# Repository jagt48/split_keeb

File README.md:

# split_keeb
Split keyboard design

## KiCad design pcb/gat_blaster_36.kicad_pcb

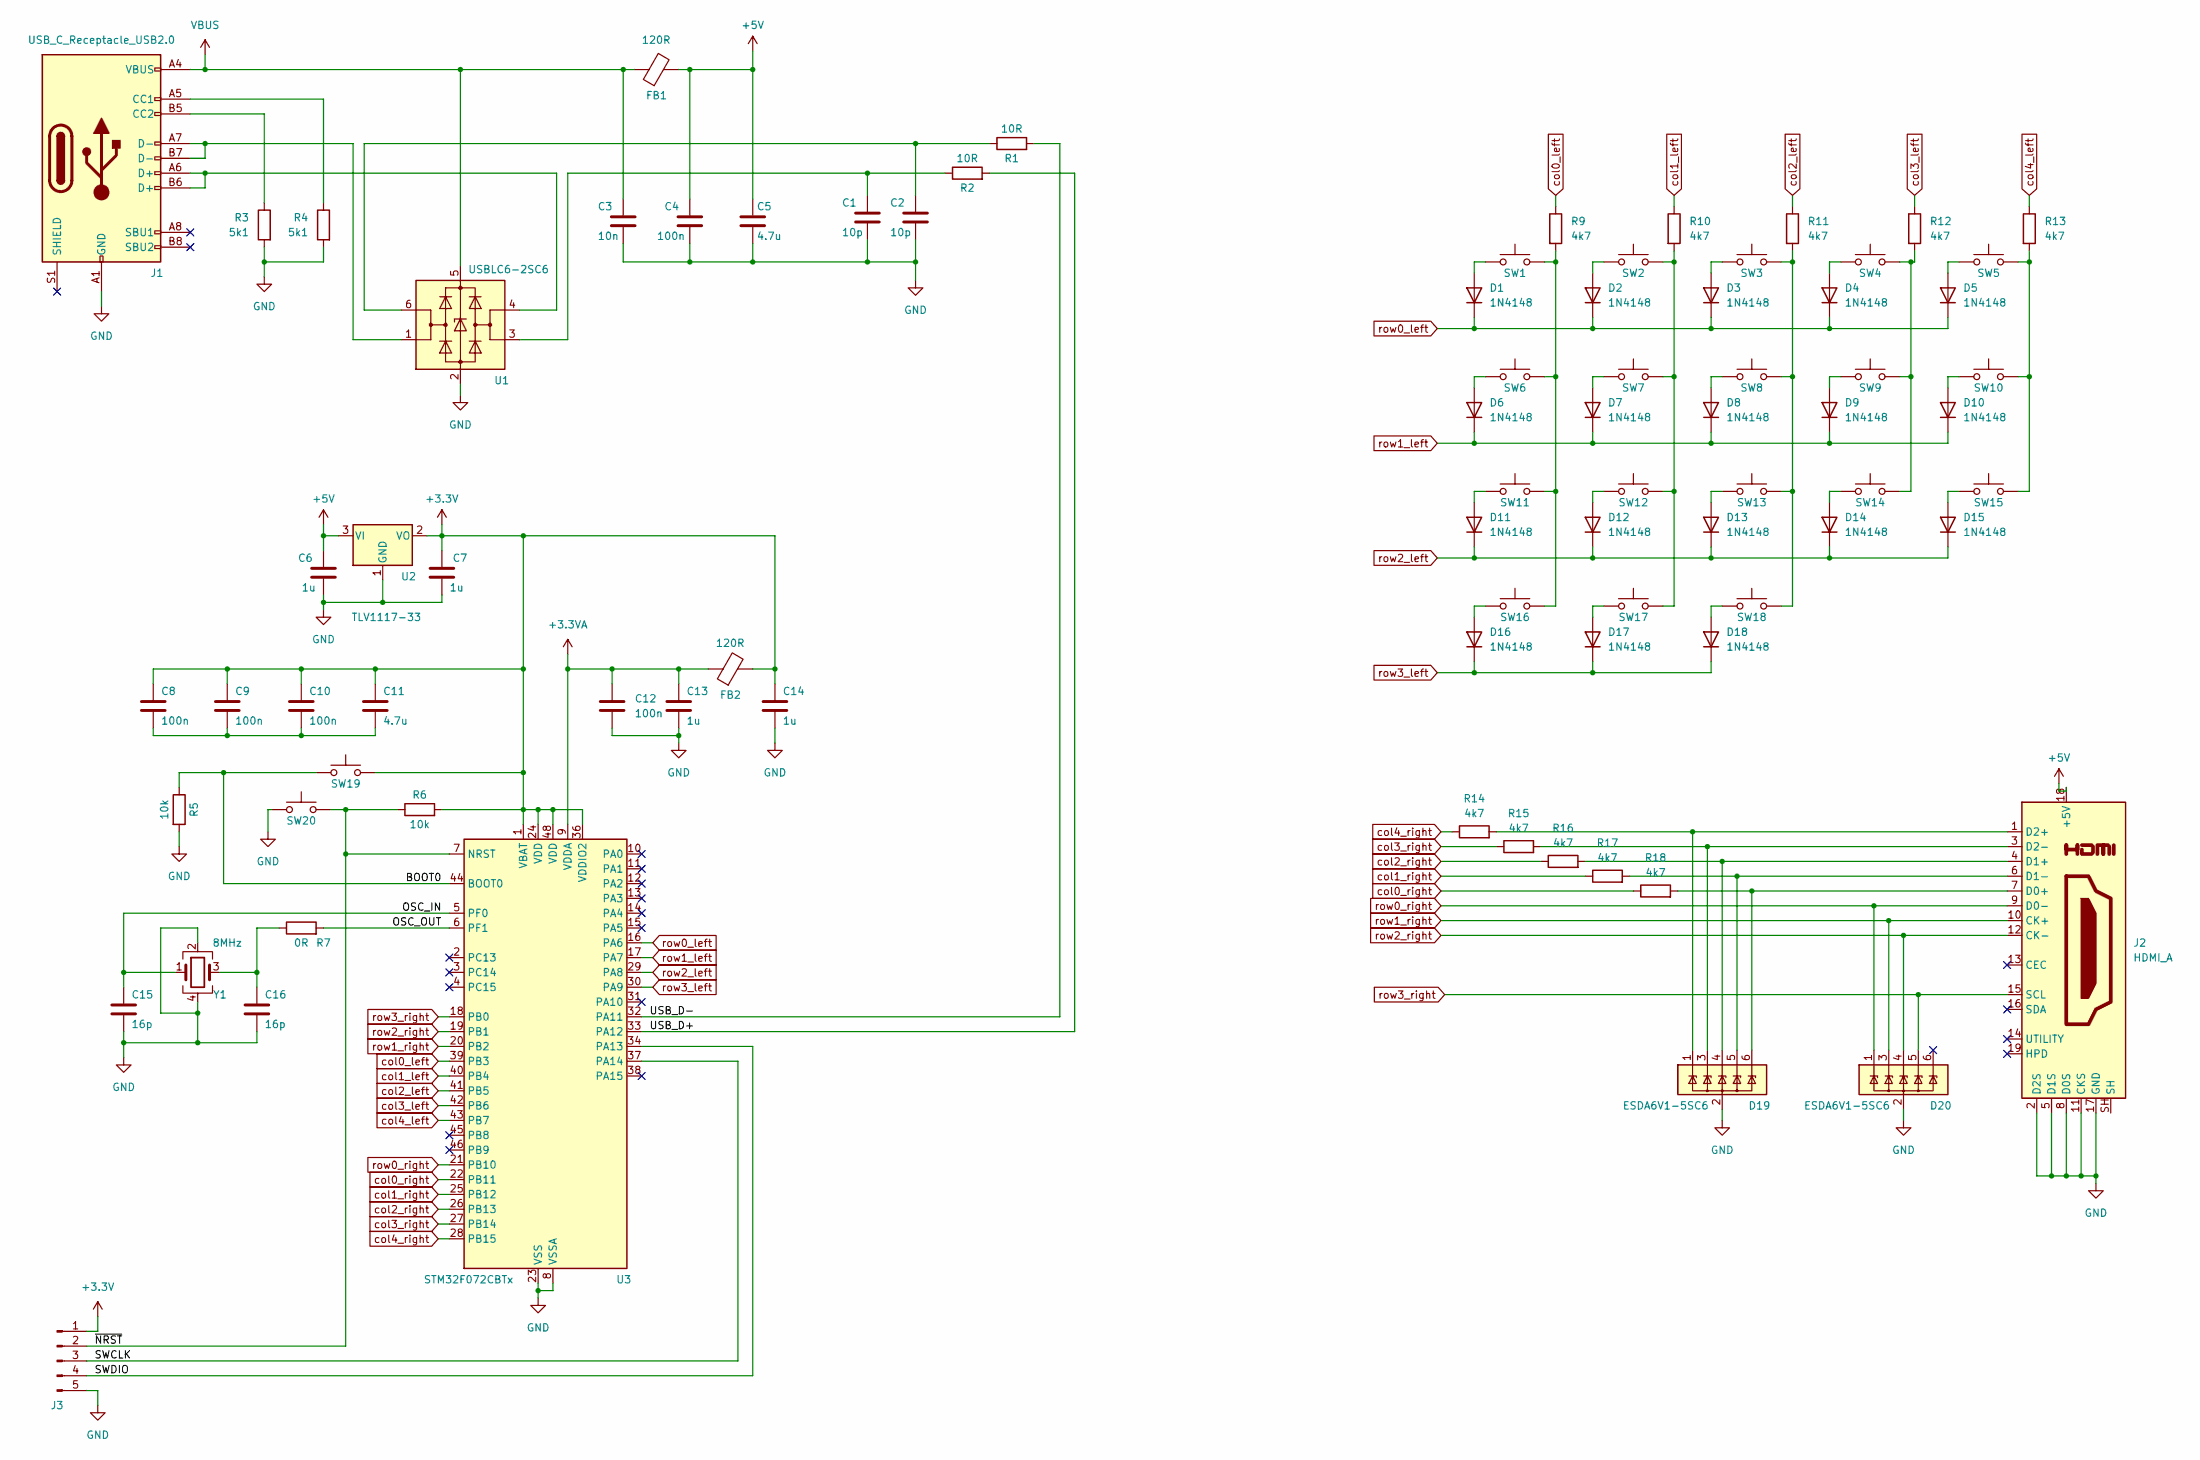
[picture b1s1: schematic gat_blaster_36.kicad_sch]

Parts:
C1, C2: 10p; 0603
C3: 10n; 0603
C4, C8, C9, C10, C12: 100n; 0603
C5, C11: 4.7u; 0603
C6, C7, C13, C14: 1u; 0603
C15, C16: 16p; 0603
D1, D2, D3, D4, D5, D6, D7, D8, D9, D10, D11, D12, D13, D14, D15, D16, D17, D18: 1N4148; sod123_mmszxxxt1g
D19, D20: ESDA6V1-5SC6; sot23-6L_usblc6-2
FB1, FB2: 120R; 0603
J1: USB_C_Receptacle_USB2.0; usb-c_usb4085
J2: HDMI_A; hdmi_cnc_tech_2000-1-1-20-00-bk
J3: Conn_01x05_Pin; SIP-5
R1, R2: 10R; 0603
R3, R4: 5k1; 0603
R5, R6: 10k; 0603
R7: 0R; 0603
R9, R10, R11, R12, R13, R14, R15, R16, R17, R18: 4k7; 0603
SW1, SW2, SW3, SW4, SW5, SW6, SW7, SW8, SW9, SW10, SW11, SW12, SW13, SW14, SW15, SW16, SW17, SW18: SW_Push; gateron_pro_5_reversible
SW19, SW20: SW_Push; sw_pts647
U1: USBLC6-2SC6; sot23-6L_usblc6-2
U2: TLV1117-33; sot223_tl1117
U3: STM32F072CBTx; QFP-48_7x7_Pitch0.5mm
Y1: 8MHz; osc_ecx-32

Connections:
+3.3V: C7.1, C8.1, C9.1, C10.1, C11.1, C14.1, FB2.2, J3.1, R6.2, SW19.2, U2.2 (VO), U3.1 (VBAT), U3.24 (VDD), U3.36 (VDDIO2), U3.48 (VDD)
+3.3VA: C12.1, C13.1, FB2.1, U3.9 (VDDA)
+5V: C4.1, C5.1, C6.1, FB1.2, J2.18 (+5V), U2.3 (VI)
/BOOT0: R5.1, SW19.1, U3.44 (BOOT0)
/OSC_IN: C15.1, U3.5 (PF0), Y1.1
/OSC_OUT: R7.2, U3.6 (PF1)
/SWCLK: J3.3, U3.37 (PA14)
/SWDIO: J3.4, U3.34 (PA13)
/USB_D+: R2.2, U3.33 (PA12)
/USB_D-: R1.2, U3.32 (PA11)
/~NRST: J3.2, R6.1, SW20.2, U3.7 (NRST)
GND: C1.2, C2.2, C3.2, C4.2, C5.2, C6.2, C7.2, C12.2, C13.2, C14.2, C15.2, C16.2, D19.2 (GND), D20.2 (GND), J1.A1 (GND), J1.A12 (GND), J1.B1 (GND), J1.B12 (GND), J2.2 (D2S), J2.5 (D1S), J2.8 (D0S), J2.11 (CKS), J2.17 (GND), J3.5, R3.2, R4.2, R5.2, SW20.1, U1.2 (GND), U2.1 (GND), U3.8 (VSSA), U3.23 (VSS), U3.35 (VSS), U3.47 (VSS), Y1.2, Y1.4
unnamed: C1.1, R2.1, U1.3 (I/O2)
unnamed: C2.1, R1.1, U1.6 (I/O1)
unnamed: C8.2, C9.2, C10.2, C11.2
unnamed: C16.1, R7.1, Y1.3
unnamed: D1.2 (A), SW1.1
unnamed: D2.2 (A), SW2.1
unnamed: D3.2 (A), SW3.1
unnamed: D4.2 (A), SW4.1
unnamed: D5.2 (A), SW5.1
unnamed: D6.2 (A), SW6.1
unnamed: D7.2 (A), SW7.1
unnamed: D8.2 (A), SW8.1
unnamed: D9.2 (A), SW9.1
unnamed: D10.2 (A), SW10.1
unnamed: D11.2 (A), SW11.1
unnamed: D12.2 (A), SW12.1
unnamed: D13.2 (A), SW13.1
unnamed: D14.2 (A), SW14.1
unnamed: D15.2 (A), SW15.1
unnamed: D16.2 (A), SW16.1
unnamed: D17.2 (A), SW17.1
unnamed: D18.2 (A), SW18.1
unnamed: D19.1 (IO1), J2.1 (D2+), R14.2
unnamed: D19.3 (IO2), J2.3 (D2-), R15.2
unnamed: D19.4 (IO3), J2.4 (D1+), R16.2
unnamed: D19.5 (IO4), J2.6 (D1-), R17.2
unnamed: D19.6 (IO5), J2.7 (D0+), R18.2
unnamed: J1.A5 (CC1), R4.1
unnamed: J1.B5 (CC2), R3.1
unnamed: J1.A6 (D+), J1.B6 (D+), U1.4 (I/O2)
unnamed: J1.A7 (D-), J1.B7 (D-), U1.1 (I/O1)
unnamed: R9.2, SW1.2, SW6.2, SW11.2, SW16.2
unnamed: R10.2, SW2.2, SW7.2, SW12.2, SW17.2
unnamed: R11.2, SW3.2, SW8.2, SW13.2, SW18.2
unnamed: R12.2, SW4.2, SW9.2, SW14.2
unnamed: R13.2, SW5.2, SW10.2, SW15.2
VBUS: C3.1, FB1.1, J1.A4 (VBUS), J1.A9 (VBUS), J1.B4 (VBUS), J1.B9 (VBUS), U1.5 (VBUS)
col0_left: R9.1, U3.39 (PB3)
col0_right: R18.1, U3.22 (PB11)
col1_left: R10.1, U3.40 (PB4)
col1_right: R17.1, U3.25 (PB12)
col2_left: R11.1, U3.41 (PB5)
col2_right: R16.1, U3.26 (PB13)
col3_left: R12.1, U3.42 (PB6)
col3_right: R15.1, U3.27 (PB14)
col4_left: R13.1, U3.43 (PB7)
col4_right: R14.1, U3.28 (PB15)
row0_left: D1.1 (K), D2.1 (K), D3.1 (K), D4.1 (K), D5.1 (K), U3.16 (PA6)
row0_right: D20.1 (IO1), J2.9 (D0-), U3.21 (PB10)
row1_left: D6.1 (K), D7.1 (K), D8.1 (K), D9.1 (K), D10.1 (K), U3.17 (PA7)
row1_right: D20.3 (IO2), J2.10 (CK+), U3.20 (PB2)
row2_left: D11.1 (K), D12.1 (K), D13.1 (K), D14.1 (K), D15.1 (K), U3.29 (PA8)
row2_right: D20.4 (IO3), J2.12 (CK-), U3.19 (PB1)
row3_left: D16.1 (K), D17.1 (K), D18.1 (K), U3.30 (PA9)
row3_right: D20.5 (IO4), J2.15 (SCL), U3.18 (PB0)

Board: 2 copper layers, 82 parts (33 on the bottom side), 67 nets, no tracks yet.

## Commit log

2023-11-05 Added micro, LDO, decoupling caps, oscillator, debeg header, boot/reset switches, and USB-C connector
2023-11-05 Added USB 5V filter
2023-11-18 Added series resistors on data lines, changed left/right communication cable to HDMI connector, fully supported by single micro.
2024-03-23 latest work from len pc
